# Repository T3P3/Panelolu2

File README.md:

Panelolu2
=========

An I2C control solution for Sanguinololu, Melzi and more

by tony@think3dprint3d.com

see
http://blog.think3dprint3d.com/2013/02/panelolu2.html
for details

GPL V3

Contents:

- Eagle files for the Panelolu2 circuit board.

- Eagle files for the Sanguinololu and Melzi adapter boards. 

- SCAD files for the case (note still a work in progress)

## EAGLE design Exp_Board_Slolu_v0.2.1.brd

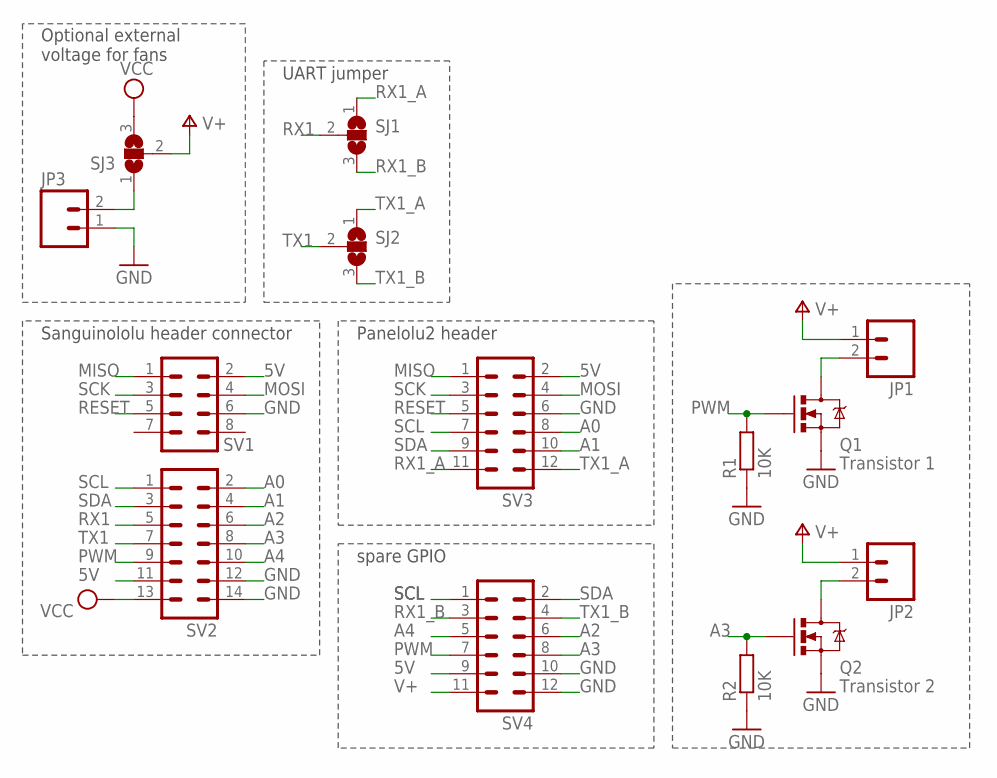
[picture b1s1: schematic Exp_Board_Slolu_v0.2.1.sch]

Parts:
JP1, JP2: M02PTH; 1X02
JP3: M02LOCK; 1X02_LOCK
Q1: Transistor 1; TO220V
Q2: Transistor 2; TO220V
R1, R2: 10K; 0204/7
SJ1, SJ2, SJ3: SJ2W; SJ_2
SV1: MA04-2
SV2: MA07-2
SV3, SV4: MA06-2

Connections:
5V: SV1.2, SV2.11, SV3.2, SV4.9
A0: SV2.2, SV3.8
A1: SV2.4, SV3.10
A2: SV2.6, SV4.6
A3: Q2.1 (G), R2.2, SV2.8, SV4.8
A4: SV2.10, SV4.5
EXT-V+: JP3.2, SJ3.1
GND: JP3.1, Q1.3 (S), Q2.3 (S), R1.1, R2.1, SV1.6, SV2.12, SV2.14, SV3.6, SV4.10, SV4.12
MISO: SV1.1, SV3.1
MOSI: SV1.4, SV3.4
unnamed: JP1.2, Q1.2 (D)
unnamed: JP2.2, Q2.2 (D)
PWM: Q1.1 (G), R1.2, SV2.9, SV4.7
RESET: SV1.5, SV3.5
RX1: SJ1.2, SV2.5
RX1_A: SJ1.1, SV3.11
RX1_B: SJ1.3, SV4.3
SCK: SV1.3, SV3.3
SCL: SV2.1, SV3.7, SV4.1
SDA: SV2.3, SV3.9, SV4.2
TX1: SJ2.2, SV2.7
TX1_A: SJ2.1, SV3.12
TX1_B: SJ2.3, SV4.4
V+: JP1.1, JP2.1, SJ3.2, SV4.11
VCC: SJ3.3, SV2.13

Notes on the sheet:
UART jumper
Sanguinololu header connector
Panelolu2 header
spare GPIO
Optional external voltage for fans

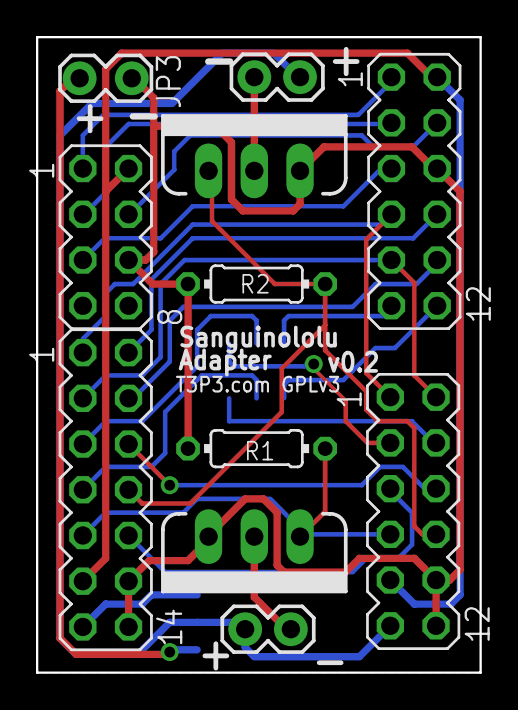
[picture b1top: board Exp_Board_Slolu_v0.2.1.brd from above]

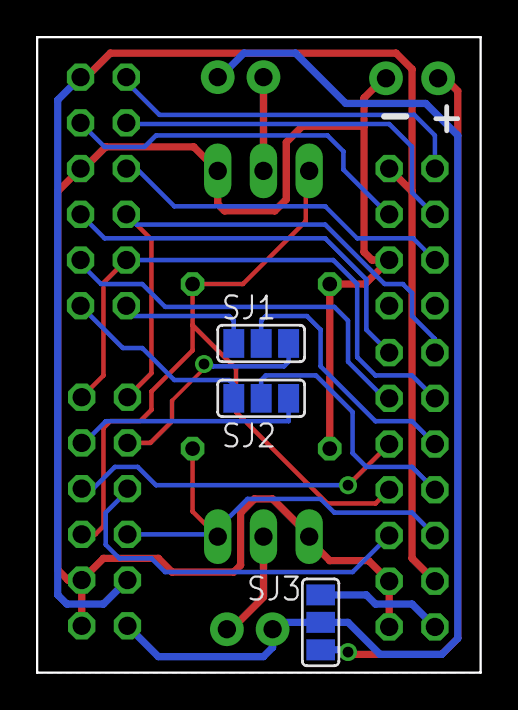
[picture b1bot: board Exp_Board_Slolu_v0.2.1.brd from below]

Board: 2 copper layers, 24.6 x 35.3 mm, 14 parts (3 on the bottom side), 25 nets.

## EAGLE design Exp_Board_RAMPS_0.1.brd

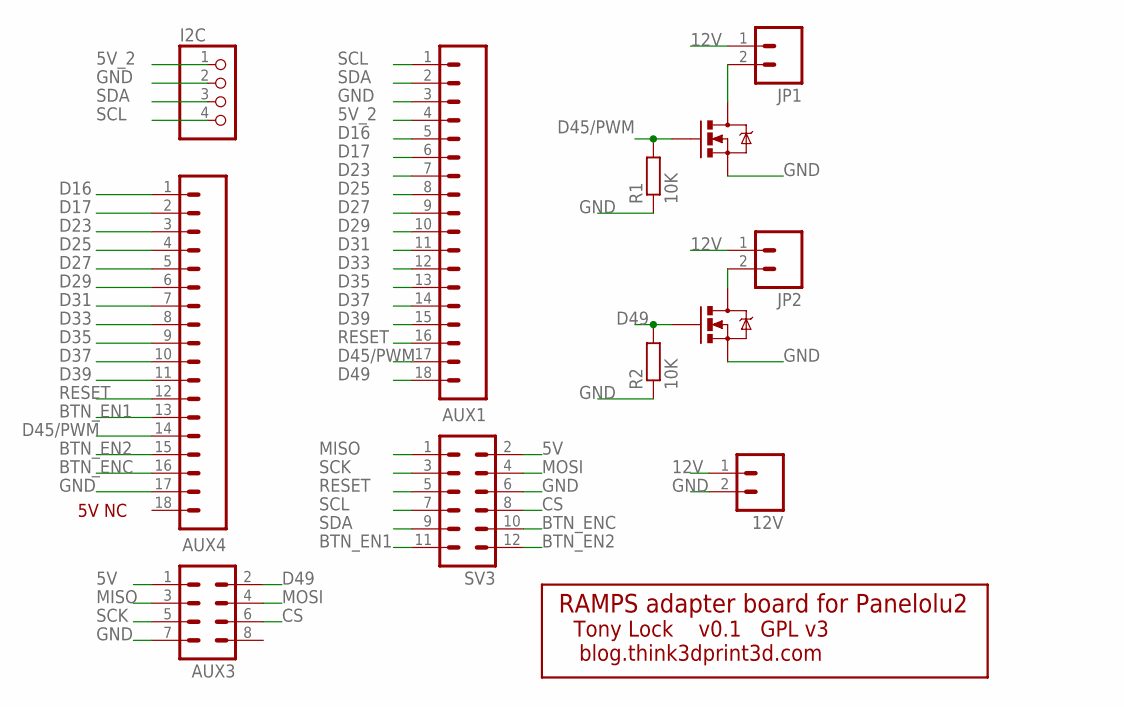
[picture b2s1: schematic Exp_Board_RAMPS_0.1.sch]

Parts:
12V: M02PTH; 1X02
AUX1, AUX4: SPARKFUN_M18_; SPARKFUN_1X18
AUX3: MA04-2
I2C: REPRAPJR_PINHD-1X4; REPRAPJR_1X04
JP1, JP2: M02PTH; 1X02
Q1: Transistor1; TO220V
Q2: Transistor2; TO220V
R1, R2: 10K; 0204/7
SV3: MA06-2_BACK

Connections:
5V: AUX3.1, SV3.2
5V_2: AUX1.4, I2C.1
12V: 12V.1, JP1.1, JP2.1
BTN_EN1: AUX4.13, SV3.11
BTN_EN2: AUX4.15, SV3.12
BTN_ENC: AUX4.16, SV3.10
CS: AUX3.6, SV3.8
D16: AUX1.5, AUX4.1
D17: AUX1.6, AUX4.2
D23: AUX1.7, AUX4.3
D25: AUX1.8, AUX4.4
D27: AUX1.9, AUX4.5
D29: AUX1.10, AUX4.6
D31: AUX1.11, AUX4.7
D33: AUX1.12, AUX4.8
D35: AUX1.13, AUX4.9
D37: AUX1.14, AUX4.10
D39: AUX1.15, AUX4.11
D45/PWM: AUX1.17, AUX4.14, Q1.1 (G), R1.2
D49: AUX1.18, AUX3.2, Q2.1 (G), R2.2
GND: 12V.2, AUX1.3, AUX3.7, AUX4.17, I2C.2, Q1.3 (S), Q2.3 (S), R1.1, R2.1, SV3.6
MISO: AUX3.3, SV3.1
MOSI: AUX3.4, SV3.4
unnamed: JP1.2, Q1.2 (D)
unnamed: JP2.2, Q2.2 (D)
RESET: AUX1.16, AUX4.12, SV3.5
SCK: AUX3.5, SV3.3
SCL: AUX1.1, I2C.4, SV3.7
SDA: AUX1.2, I2C.3, SV3.9

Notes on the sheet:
RAMPS adapter board for Panelolu2
Tony Lock v0.1 GPL v3
blog.think3dprint3d.com
5V NC

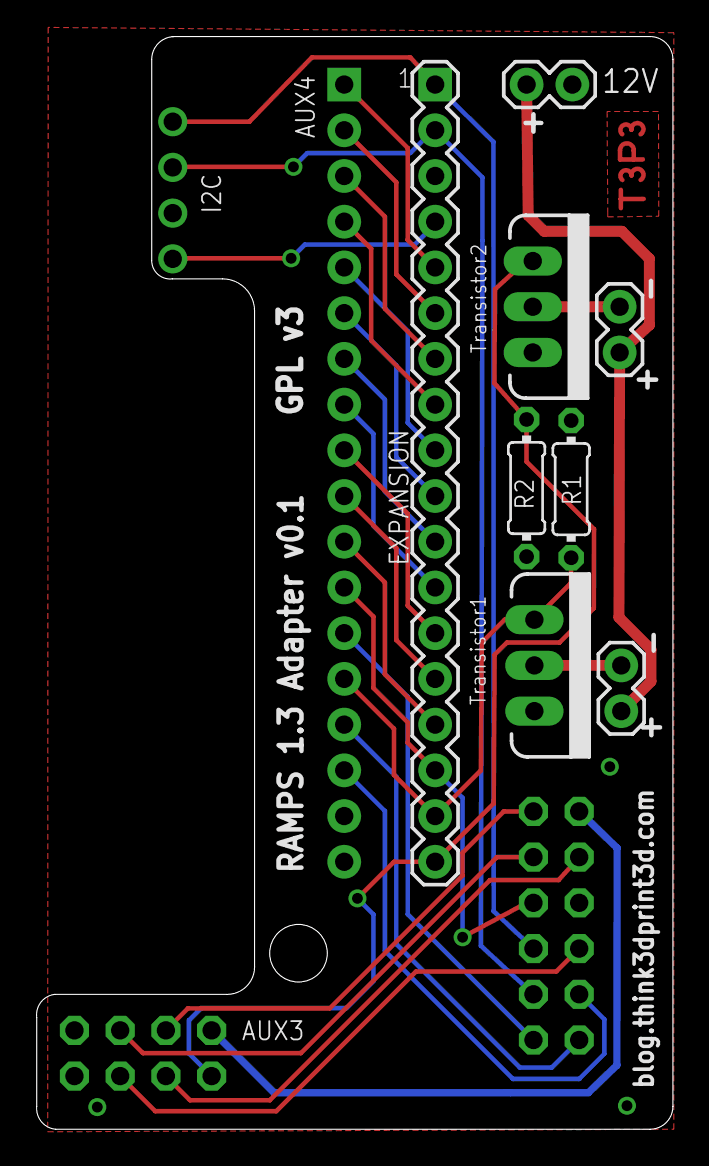
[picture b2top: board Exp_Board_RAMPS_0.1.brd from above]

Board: 2 copper layers, 35.4 x 60.7 mm, 12 parts (0 on the bottom side), 29 nets.

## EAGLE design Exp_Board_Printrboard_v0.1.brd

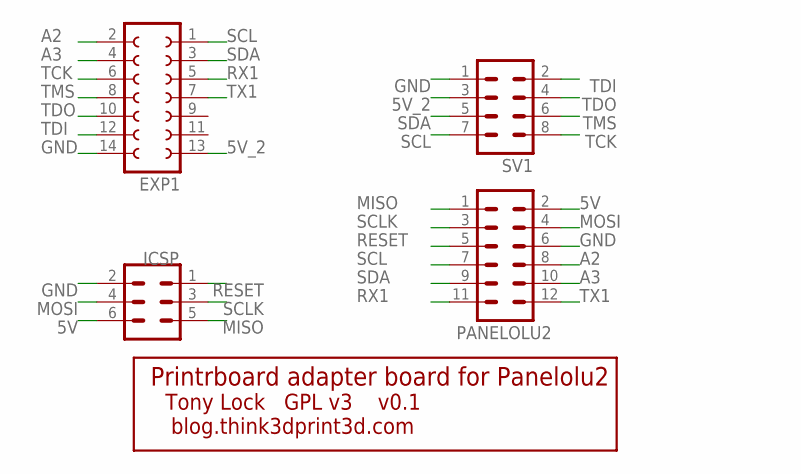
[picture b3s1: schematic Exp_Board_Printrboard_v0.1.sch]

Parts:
EXP1: FE07-2
ICSP: MA03-2
PANELOLU2: MA06-2_BACK
SV1: MA04-2

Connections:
5V: ICSP.6, PANELOLU2.2
5V_2: EXP1.13, SV1.3
A2: EXP1.2, PANELOLU2.8
A3: EXP1.4, PANELOLU2.10
GND: EXP1.14, ICSP.2, PANELOLU2.6, SV1.1
MISO: ICSP.5, PANELOLU2.1
MOSI: ICSP.4, PANELOLU2.4
RESET: ICSP.1, PANELOLU2.5
RX1: EXP1.5, PANELOLU2.11
SCL: EXP1.1, PANELOLU2.7, SV1.7
SCLK: ICSP.3, PANELOLU2.3
SDA: EXP1.3, PANELOLU2.9, SV1.5
TCK: EXP1.6, SV1.8
TDI: EXP1.12, SV1.2
TDO: EXP1.10, SV1.4
TMS: EXP1.8, SV1.6
TX1: EXP1.7, PANELOLU2.12

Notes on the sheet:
Printrboard adapter board for Panelolu2
Tony Lock GPL v3 v0.1
blog.think3dprint3d.com

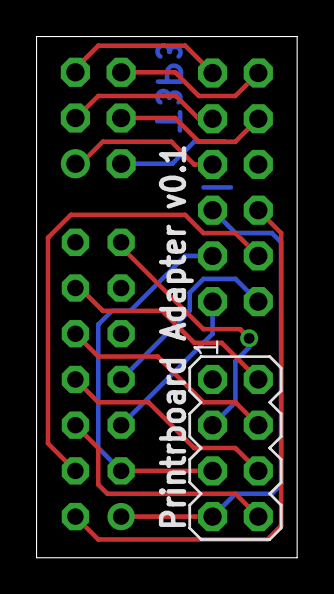
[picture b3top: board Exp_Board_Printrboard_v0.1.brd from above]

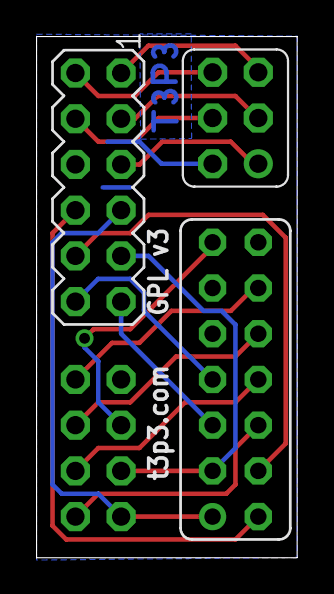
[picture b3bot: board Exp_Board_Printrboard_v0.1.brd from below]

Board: 2 copper layers, 14.5 x 29.0 mm, 4 parts (2 on the bottom side), 17 nets.

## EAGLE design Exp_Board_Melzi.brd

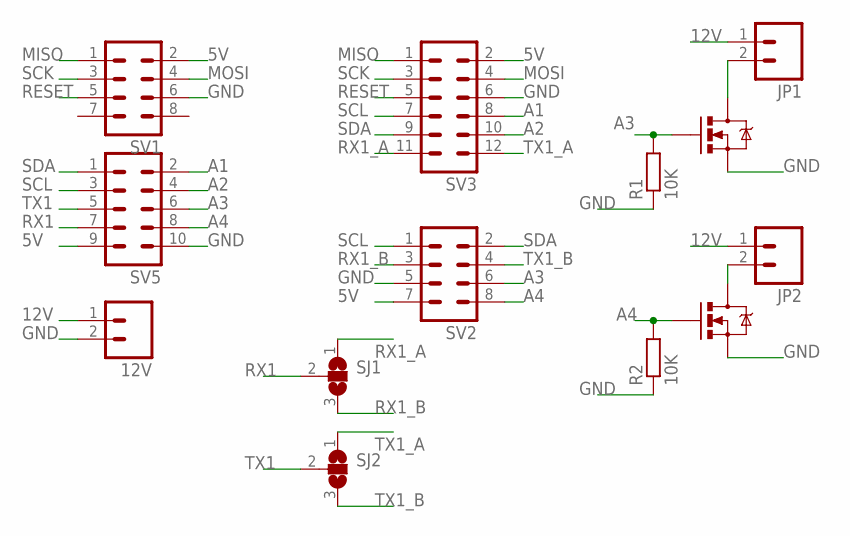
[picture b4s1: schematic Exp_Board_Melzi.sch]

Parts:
12V: M02PTH; 1X02
JP1, JP2: M02PTH; 1X02
Q1: Transistor1; TO220V
Q2: Transistor2; TO220V
R1, R2: 10K; 0204/7
SJ1, SJ2: SJ2W; SJ_2
SV1, SV2: MA04-2
SV3: MA06-2
SV5: MA05-2

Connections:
5V: SV1.2, SV2.7, SV3.2, SV5.9
12V: JP1.1, JP2.1
A1: SV3.8, SV5.2
A2: SV3.10, SV5.4
A3: Q1.1 (G), R1.2, SV2.6, SV5.6
A4: Q2.1 (G), R2.2, SV2.8, SV5.8
GND: Q1.3 (S), Q2.3 (S), R1.1, R2.1, SV1.6, SV2.5, SV3.6, SV5.10
MISO: SV1.1, SV3.1
MOSI: SV1.4, SV3.4
unnamed: JP1.2, Q1.2 (D)
unnamed: JP2.2, Q2.2 (D)
RESET: SV1.5, SV3.5
RX1: SJ1.2, SV5.7
RX1_A: SJ1.1, SV3.11
RX1_B: SJ1.3, SV2.3
SCK: SV1.3, SV3.3
SCL: SV2.1, SV3.7, SV5.3
SDA: SV2.2, SV3.9, SV5.1
TX1: SJ2.2, SV5.5
TX1_A: SJ2.1, SV3.12
TX1_B: SJ2.3, SV2.4

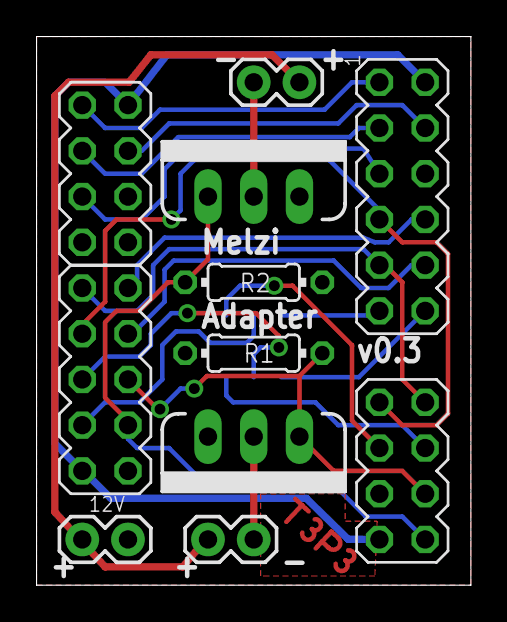
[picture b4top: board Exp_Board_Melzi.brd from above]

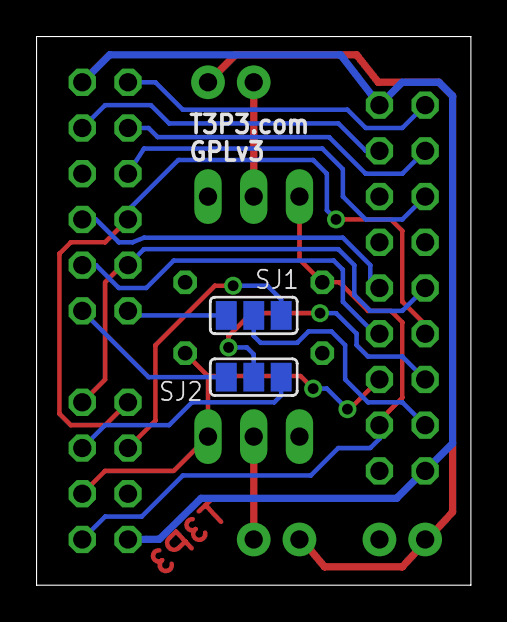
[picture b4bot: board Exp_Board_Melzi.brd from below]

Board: 2 copper layers, 24.1 x 30.5 mm, 13 parts (2 on the bottom side), 21 nets.

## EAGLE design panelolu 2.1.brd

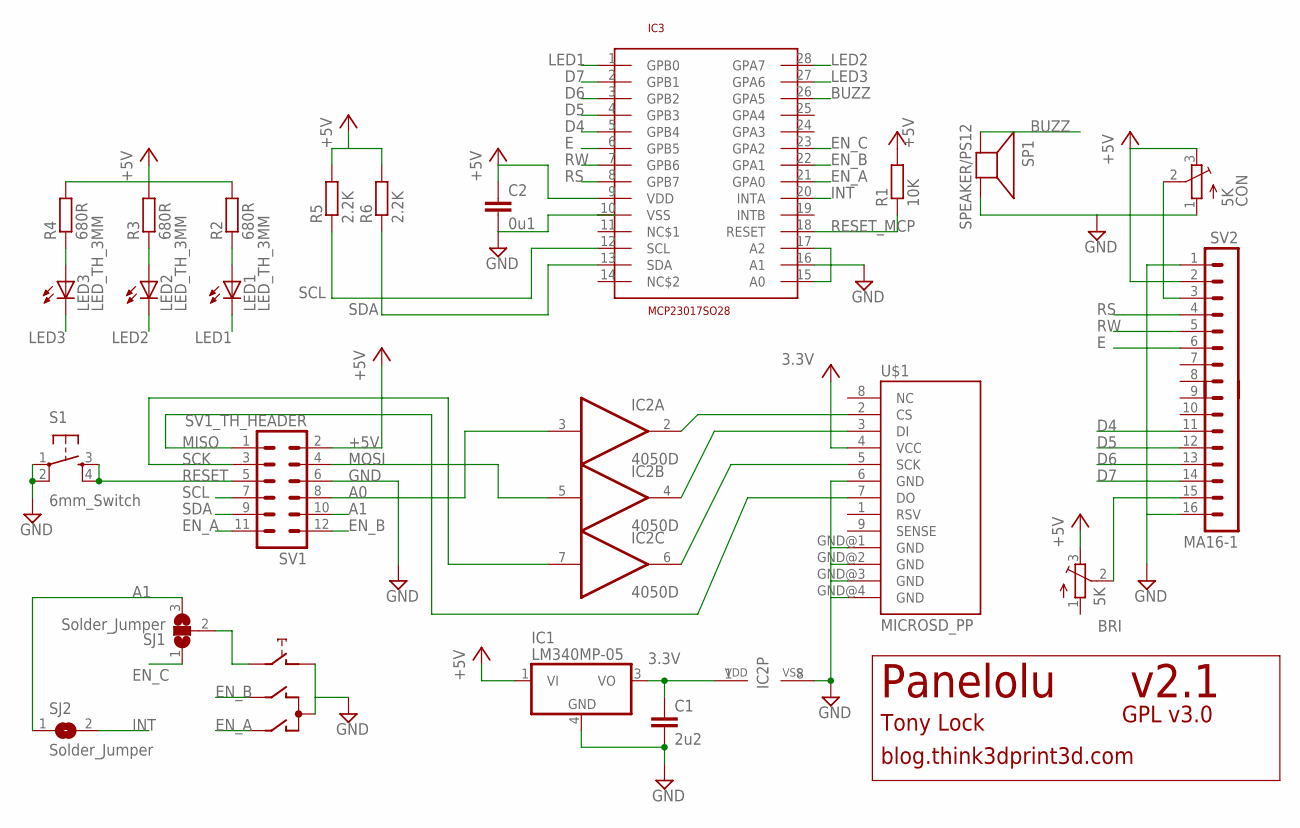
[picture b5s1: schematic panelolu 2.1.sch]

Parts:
BRI: 5K; TC33X
C1: 2u2; C1206K
C2: 0u1; C0805K
CON: 5K; TC33X
IC1: LM340MP-05; SOT223
IC2: 4050D; SO16
IC3: MCP23017SO28; SO28W
LED1, LED2, LED3: LED_TH_3MM; LED3MM
R1: 10K; M0805
R2, R3, R4: 680R; M0805
R5, R6: 2.2K; M0805
S1: 6mm_Switch; TACTILE-PTH
SJ1: Solder_Jumper; SJ_2
SJ2: Solder_Jumper; SJ
SP1: SPEAKER/PS12; PS12
SV1: SV1_TH_HEADER; MA06-2
SV2: MA16-1
SW1: EC12E_SW; ALPS_EC12E_SW
U$1: MICROSD_PP

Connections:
3.3V: C1.1, IC1.3 (VO), IC2.1 (VDD), U$1.4 (VCC)
+5V: BRI.3 (E), C2.1, CON.3 (E), IC1.1 (VI), IC3.9 (VDD), R1.2, R2.2, R3.2, R4.2, R5.2, R6.2, SV1.2, SV2.2
A0: IC2.3 (I), SV1.8
A1: SJ1.3, SJ2.1, SV1.10
BUZZ: IC3.26 (GPA5), SP1.P$1 (+)
CS3.3: IC2.2 (O), U$1.2 (CS)
D4: IC3.5 (GPB4), SV2.11
D5: IC3.4 (GPB3), SV2.12
D6: IC3.3 (GPB2), SV2.13
D7: IC3.2 (GPB1), SV2.14
DI3.3: IC2.4 (O), U$1.3 (DI)
E: IC3.6 (GPB5), SV2.6
EN_A: IC3.21 (GPA0), SV1.11, SW1.A
EN_B: IC3.22 (GPA1), SV1.12, SW1.B
EN_C: IC3.23 (GPA2), SJ1.1
GND: C1.2, C2.2, CON.1 (A), IC1.4 (GND), IC2.8 (VSS), IC3.10 (VSS), IC3.15 (A0), IC3.16 (A1), IC3.17 (A2), S1.1, S1.2, SP1.P$2 (-), SV1.6, SV2.1, SV2.16, SW1.C, SW1.D (1), U$1.6 (GND), U$1.GND@1 (GND), U$1.GND@2 (GND), U$1.GND@3 (GND), U$1.GND@4 (GND)
INT: IC3.20 (INTA), SJ2.2
LED1: IC3.1 (GPB0), LED1.K (C)
LED2: IC3.28 (GPA7), LED2.K (C)
LED3: IC3.27 (GPA6), LED3.K (C)
MISO: SV1.1, U$1.7 (DO)
MOSI: IC2.5 (I), SV1.4
unnamed: BRI.2 (S), SV2.15
unnamed: CON.2 (S), SV2.3
unnamed: LED1.A, R2.1
unnamed: LED2.A, R3.1
unnamed: LED3.A, R4.1
unnamed: SJ1.2, SW1.E (2)
RESET: S1.3, S1.4, SV1.5
RESET_MCP: IC3.18 (RESET), R1.1
RS: IC3.8 (GPB7), SV2.4
RW: IC3.7 (GPB6), SV2.5
SCK: IC2.7 (I), SV1.3
SCK3.3: IC2.6 (O), U$1.5 (SCK)
SCL: IC3.12 (SCL), R5.1, SV1.7
SDA: IC3.13 (SDA), R6.1, SV1.9

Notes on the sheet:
v2.1
blog.think3dprint3d.com
Tony Lock
GPL v3.0
Panelolu

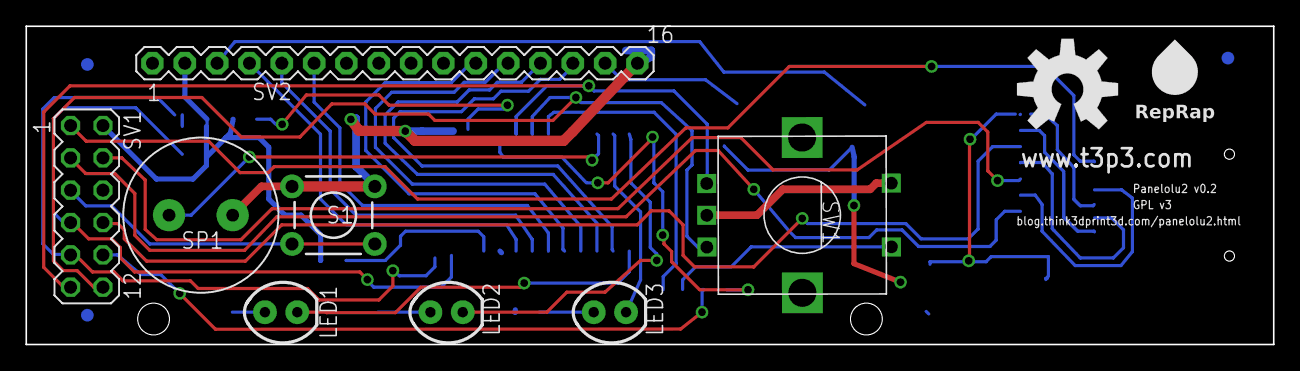
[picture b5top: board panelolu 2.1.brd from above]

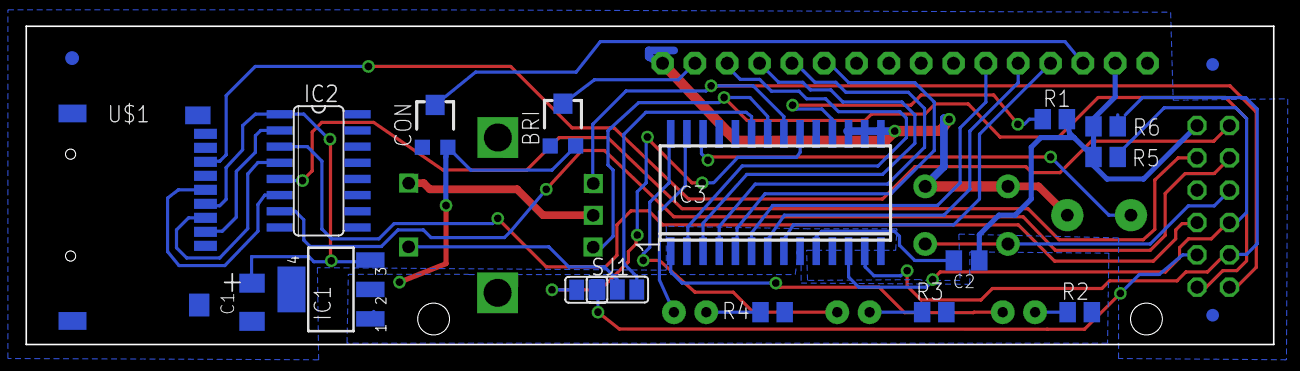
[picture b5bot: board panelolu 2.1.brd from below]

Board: 2 copper layers, 98.0 x 25.0 mm, 24 parts (16 on the bottom side), 36 nets.

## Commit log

2013-02-15 initial upload of files
2013-02-15 Added correct link to blog post
2013-02-18 added bitmap_32.scad and made minor changes to contrast and brightness holes
2013-04-09 Slight amendment of schematic
2013-04-24 Added RAMPS1.3 and Printrboard adapter CAD files
2013-10-27 Update README.md
    fixed typo
2014-09-22 Added external voltage for fans
    Added an external input for the fans and 12v output, as printers might
    run at 19v (huxley) or even 24v (my huxley) I also tidied the Schematics
    up, and routhed all ground traces to give a better overview of what
    paths ground has to take with the pour.
    Also added pour to the bottom layer

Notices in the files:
Exp_Board_Printrboard_v0.1.brd:
t3p3.com GPL v3
parts and their libraries:
SparkFun-DiscreteSemi: Licensing: CC v3.0 Share-Alike You are welcome to use this library for commercial purposes.
